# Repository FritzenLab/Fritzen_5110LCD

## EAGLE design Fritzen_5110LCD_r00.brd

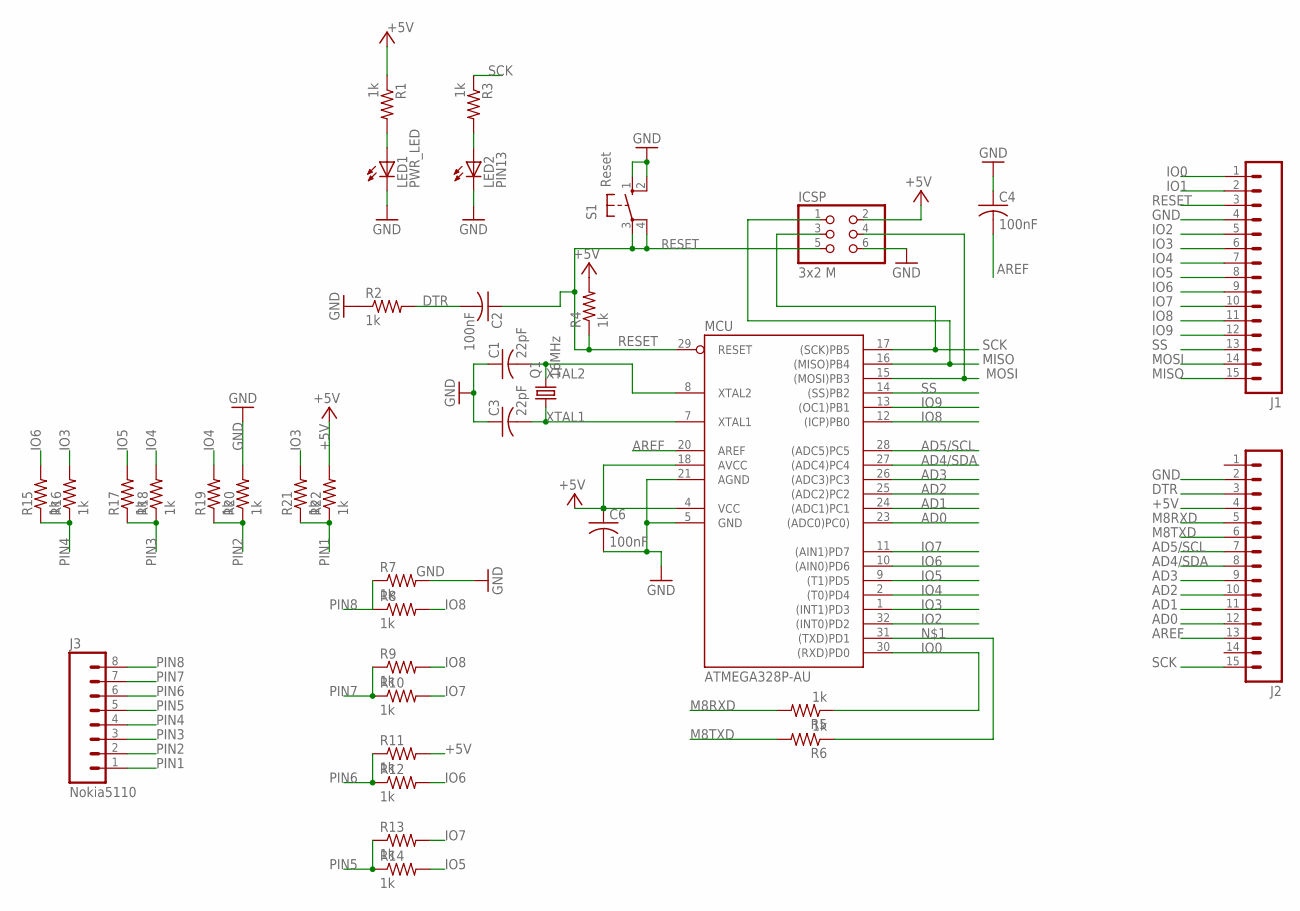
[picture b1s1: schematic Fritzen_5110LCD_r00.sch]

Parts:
C1, C3: 22pF; C0805
C2, C4, C6: 100nF; C0805
ICSP: 3x2 M; 2X03
J1, J2: M15; 1X15
J3: Nokia5110; 1X08
LED1: PWR_LED; CHIPLED_0805
LED2: PIN13; CHIPLED_0805
MCU: ATMEGA328P-AU; TQFP32-08
Q1: 16MHz; HC49/S
R1, R2, R3, R4, R5, R6, R7, R8, R9, R10, R11, R12, R13, R14, R15, R16, R17, R18, R19, R20, R21, R22: 1k; M0805
S1: Reset; B3F-10XX

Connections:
+5V: C6.1, ICSP.2, J2.4, MCU.4 (VCC), MCU.18 (AVCC), R1.1, R4.2, R11.2, R22.2
AD0: J2.12, MCU.23 ((ADC0)PC0))
AD1: J2.11, MCU.24 ((ADC1)PC1)
AD2: J2.10, MCU.25 ((ADC2)PC2)
AD3: J2.9, MCU.26 ((ADC3)PC3)
AD4/SDA: J2.8, MCU.27 ((ADC4)PC4)
AD5/SCL: J2.7, MCU.28 ((ADC5)PC5)
AREF: C4.2, J2.13, MCU.20 (AREF)
DTR: C2.2, J2.3, R2.2
GND: C1.1, C3.1, C4.1, C6.2, ICSP.6, J1.4, J2.2, LED1.C, LED2.C, MCU.5 (GND), MCU.21 (AGND), R2.1, R7.2, R20.2, S1.1 (S), S1.2 (S1)
IO0: J1.1, MCU.30 ((RXD)PD0), R5.1
IO1: J1.2, R6.1
IO2: J1.5, MCU.32 ((INT0)PD2)
IO3: J1.6, MCU.1 ((INT1)PD3), R16.2, R21.2
IO4: J1.7, MCU.2 ((T0)PD4), R18.2, R19.2
IO5: J1.8, MCU.9 ((T1)PD5), R14.2, R17.2
IO6: J1.9, MCU.10 ((AIN0)PD6), R12.2, R15.2
IO7: J1.10, MCU.11 ((AIN1)PD7), R10.2, R13.2
IO8: J1.11, MCU.12 ((ICP)PB0), R8.2, R9.2
IO9: J1.12, MCU.13 ((OC1)PB1)
M8RXD: J2.5, R5.2
M8TXD: J2.6, R6.2
MISO: ICSP.1, J1.15, MCU.16 ((MISO)PB4)
MOSI: ICSP.4, J1.14, MCU.15 ((MOSI)PB3)
unnamed: LED2.A, R3.2
unnamed: LED1.A, R1.2
PIN1: J3.1, R21.1, R22.1
PIN2: J3.2, R19.1, R20.1
PIN3: J3.3, R17.1, R18.1
PIN4: J3.4, R15.1, R16.1
PIN5: J3.5, R13.1, R14.1
PIN6: J3.6, R11.1, R12.1
PIN7: J3.7, R9.1, R10.1
PIN8: J3.8, R7.1, R8.1
RESET: C2.1, ICSP.5, J1.3, MCU.29 (RESET), R4.1, S1.3, S1.4 (P1)
SCK: ICSP.3, J2.15, MCU.17 ((SCK)PB5), R3.1
SS: J1.13, MCU.14 ((SS)PB2)
XTAL1: C3.2, MCU.7 (XTAL1), Q1.1
XTAL2: C1.2, MCU.8 (XTAL2), Q1.2

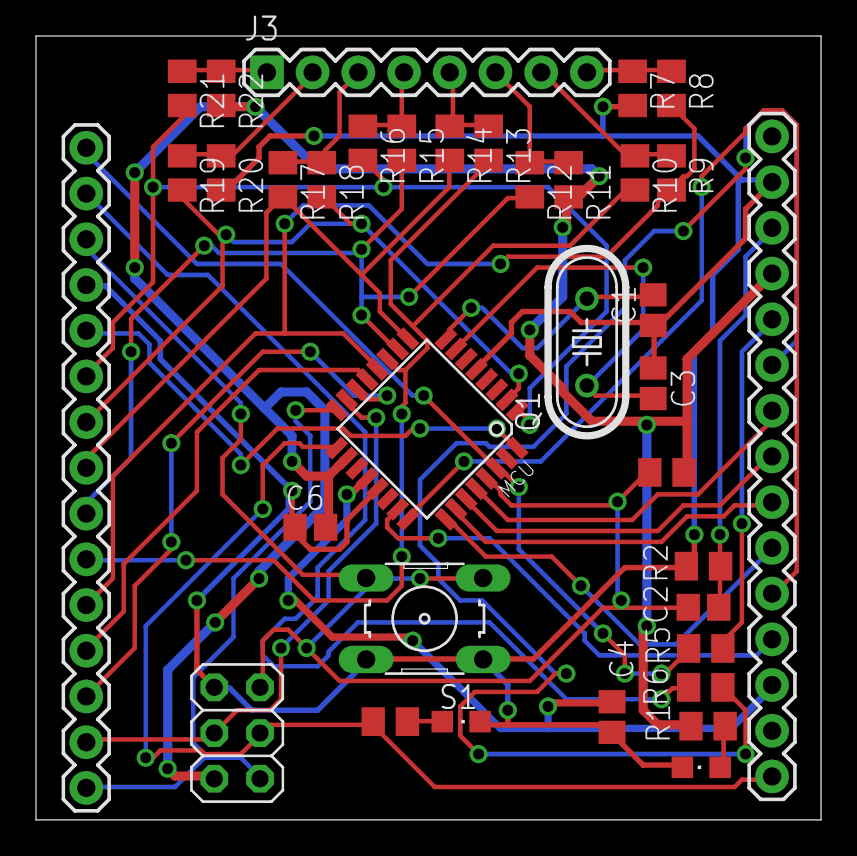
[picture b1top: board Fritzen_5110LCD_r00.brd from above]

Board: 2 copper layers, 43.6 x 43.6 mm, 36 parts (0 on the bottom side), 39 nets.

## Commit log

2016-03-12 Initial release
    Do not use or copy this files (and mainly: do not order this PCB's, they
    won't work). This is work in progress

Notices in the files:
parts and their libraries:
SparkFun-Connectors: Licensing: Creative Commons ShareAlike 4.0 International - https://creativecommons.org/licenses/by-sa/4.0
